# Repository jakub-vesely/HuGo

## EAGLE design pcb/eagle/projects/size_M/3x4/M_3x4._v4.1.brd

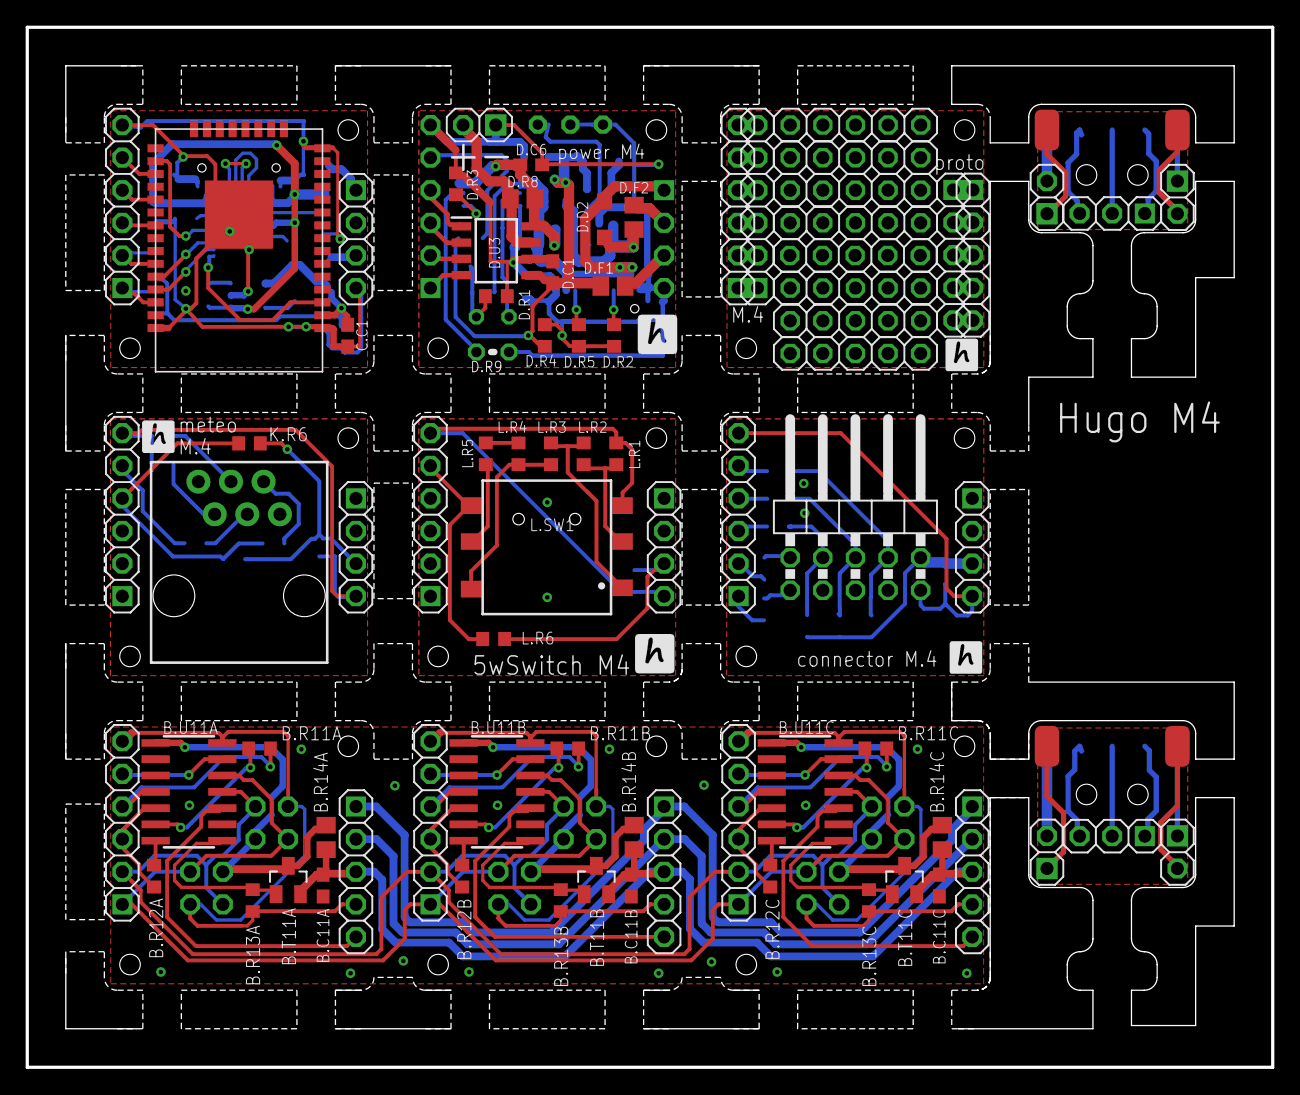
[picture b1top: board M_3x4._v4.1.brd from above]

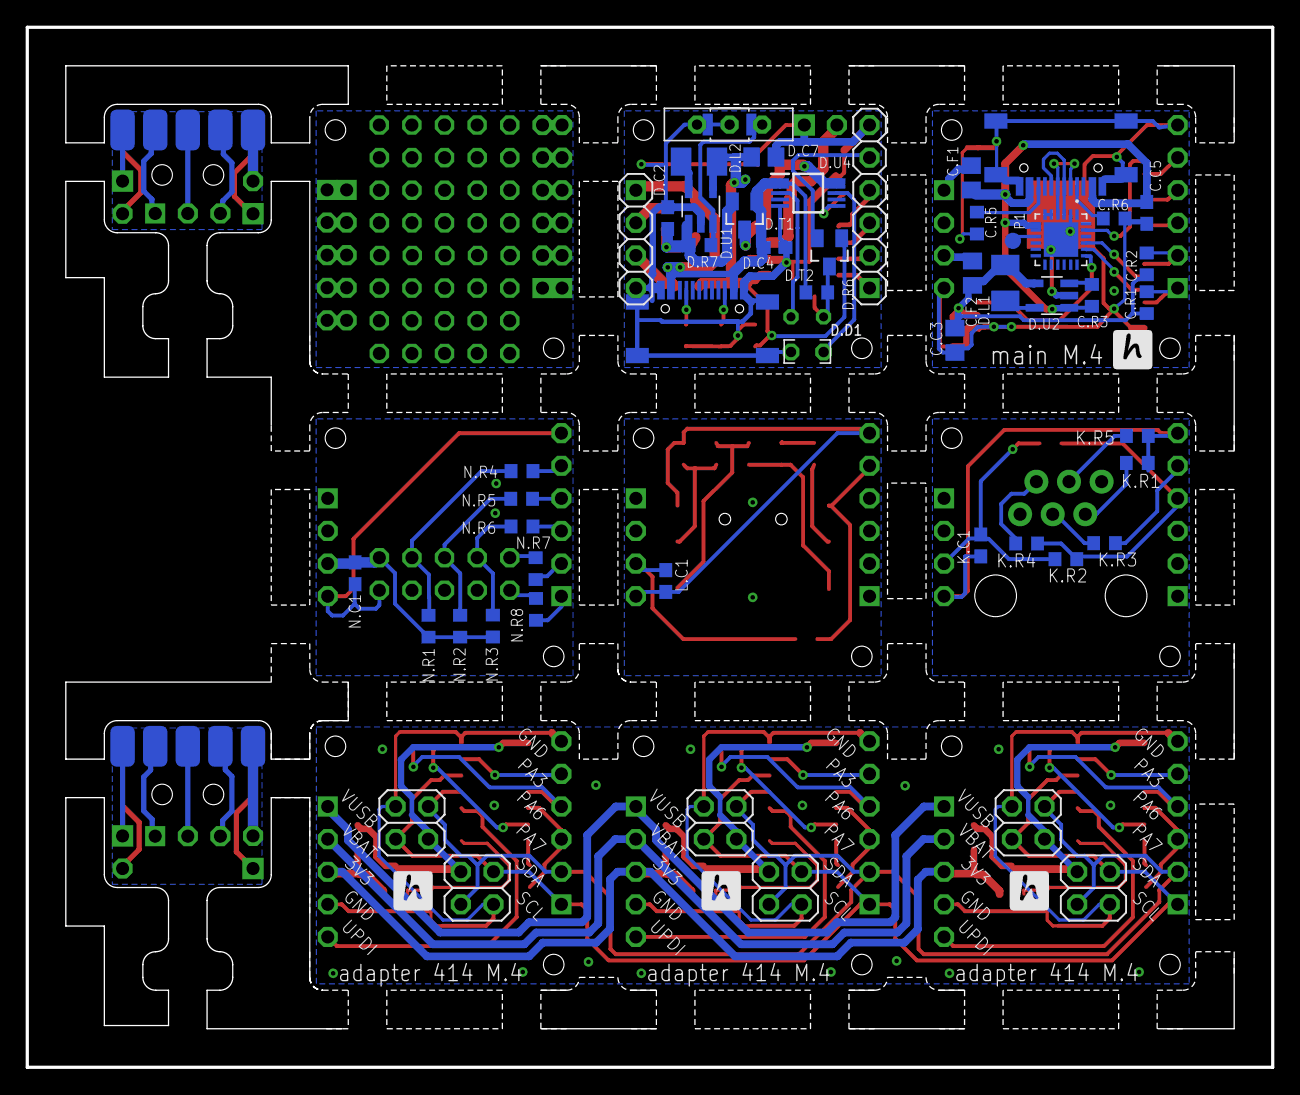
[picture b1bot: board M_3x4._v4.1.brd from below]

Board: 2 copper layers, 97.0 x 81.0 mm, 132 parts (51 on the bottom side), 125 nets.

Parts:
B.C11A, B.C11B, B.C11C: 100n; C0603
B.J1, B.J5, B.J12: 1X06
B.J2, B.J3, B.J6, B.J7, B.J13, B.J14: 2X02
B.J4, B.J8, B.J11: 1X05
B.R11A, B.R11B, B.R11C: alt RX 0R; R0603
B.R12A, B.R12B, B.R12C: alt TX 0R; R0603
B.R13A, B.R13B, B.R13C: 100k; R0603
B.R14A, B.R14B, B.R14C: alt fuse or 0R; FUSE
B.T11A, B.T11B, B.T11C: NX3008; SO23
B.U11A, B.U11B, B.U11C: AT414; SO14
C.C1: 100n; C0603
C.C3: 22u; C0805
C.C5: 1u; C0603
C.F1, C.F2: 0.5A; R0805
C.J2: 1X06
C.R1, C.R2: 2k2; R0603
C.R3: 100k; R0603
C.R5: 5K1; R0603
C.R6: 5k1; R0603
C.U1: TTGO-MICRO-32
D.C1: 100n; C0603
D.C2, D.C4, D.C6: 4u7; C0603
D.C7: 10u; C0805
D.D1: LED_1.8_FLIPPED; LED_1.8
D.D2: SHOTKY_2.8
D.F1: 0.5A; R0805
D.F2: 1.1A; R0805
D.J2: 1X06
D.J3: 1X04
D.L1, D.L2: 2u2; L3230M
D.LIPOL: 1X02
D.ON/OFF/RESET: SWITCH
D.R1: 4k7; R0603
D.R2, D.R5: 5k1; R0603
D.R3: I=1/R (4k7 for 213mA, 2k2 for455mA ); R0603
D.R4: 100k; R0603
D.R6: 3k3; R0603
D.R7: 390k; R0603
D.R8: 0.1; R0805
D.R9: TERM_10K; THERM
D.T1: FDV304; SO23
D.T2: NX3008; SO23
D.U1, D.U2: LM3671_3.3; SOT32-5
D.U3: INA219AIDR; SOIC127P600X175-8N
D.U4: MCP73833-AMI_UN; SOP50P490X110-10N
G.J1: 1X06
G.J2: 1X04
I.J1, I.J3: 1X04
J1: RJ11; RJ11-6
JP1: 1X04
JP2, JP3, JP5, JP9: 1X06
JP4, JP11: 1X05
JP6, JP12: 1X03
JP7, JP8, JP13, JP14: 1X02
JP10: 2X05/90
K.C1: 100n; C0603
K.R1, K.R3, K.R4, K.R5: 1k; R0603
K.R2, K.R6: 4k7; R0603
L.C1: 100n; C0603
L.R1, L.R2: 1k; R0603
L.R3, L.R4, L.R5, L.R6: 2k2; R0603
L.SW1: 5_WAY_SWITCH
N.C1: 100n; C0603
N.R1, N.R2, N.R3, N.R4, N.R5, N.R6, N.R7, N.R8: 4k7; R0603
P1: TPB1,27; B1,27
U1: CP2104-F03-GM; QFN50P400X400X80-25N
U$1, U$2: USB-C
U$3, U$4, U$5, U$6, U$7, U$8, U$9, U$10: PINHD-1X5_AUTO; 1X5_AUTO
U$11, U$12: 7PIN_CONNECTOR

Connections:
3V3F: D.F1.2, D.J3.3
GND: C.C1.2, C.C3.2, C.C5.1, C.J2.6, C.R5.1, C.R6.1, C.U1.GND1, C.U1.GND2, C.U1.GND3, C.U1.GND4, C.U1.GND5, C.U1.GND6, C.U1.GND7, C.U1.GND8, C.U1.GND9, C.U1.GND10, C.U1.GND11, D.U2.GND, JP1.4, U1.2, U1.25, U$1.A1B12, U$1.B1A12, U$1.SH1, U$1.SH2, U$1.SH3, U$1.SH4
GND1: D.C1.1, D.C2.1, D.C4.1, D.C6.1, D.C7.1, D.J2.6, D.J3.4, D.LIPOL.1, D.ON/OFF/RESET.P$1, D.ON/OFF/RESET.P$2, D.ON/OFF/RESET.P$4, D.R1.1, D.R2.2, D.R3.1, D.R4.2, D.R5.2, D.R9.1, D.U1.GND, D.U3.6, D.U4.5, U$2.A1B12, U$2.B1A12, U$2.SH1, U$2.SH2, U$2.SH3, U$2.SH4
GND2: JP2.6, JP3.6, JP4.4, JP11.4
GND3: G.J1.6, G.J2.4, L.C1.1, L.R1.2, L.SW1.4
GND4: I.J3.4, JP5.6, K.C1.2, K.R1.1, K.R5.1
GND5: JP7.1, U$11.7
GND6: B.C11A.2, B.C11B.2, B.C11C.2, B.J1.6, B.J2.4, B.J3.1, B.J4.4, B.J5.6, B.J6.4, B.J7.1, B.J8.4, B.J11.4, B.J12.6, B.J13.4, B.J14.1, B.R13A.2, B.R13B.2, B.R13C.2, B.U11A.14, B.U11B.14, B.U11C.14
GND7: I.J1.4, JP9.6, JP10.9, N.C1.2
GND8: JP13.1, U$12.7
IN+: D.LIPOL.2, D.R8.2, D.U3.7
IN-: D.C6.2, D.R8.1, D.T1.D, D.U3.8, D.U4.9, D.U4.10
unnamed: U1.4, U$1.A7, U$1.B7
unnamed: U1.3, U$1.A6, U$1.B6
unnamed: C.R6.2, U$1.A5
unnamed: C.R5.2, U$1.B5
unnamed: C.F2.2, JP1.3
unnamed: C.F1.2, JP1.1
unnamed: P1.TP, U1.9
unnamed: U1.5, U1.6
unnamed: D.L2.1, D.U1.VOUT
unnamed: D.L1.1, D.U2.VOUT
unnamed: C.R3.1, D.U2.SHDN
unnamed: C.J2.5, C.U1.IO4
unnamed: C.J2.4, C.U1.IO17
unnamed: C.J2.3, C.U1.IO18
unnamed: D.ON/OFF/RESET.P$3, D.ON/OFF/RESET.P$5, D.R7.2, D.U1.SHDN
unnamed: D.R5.1, U$2.B5
unnamed: D.R2.1, U$2.A5
unnamed: D.R3.2, D.U4.6
unnamed: D.R9.2, D.U4.8
unnamed: D.J2.5, D.T2.S
unnamed: JP2.5, JP3.5
unnamed: JP2.4, JP3.4
unnamed: JP2.3, JP3.3
unnamed: JP2.2, JP3.2
unnamed: JP2.1, JP3.1
unnamed: JP4.5, JP11.5
unnamed: JP4.2, JP11.2
unnamed: JP4.1, JP11.1
unnamed: JP4.3, JP11.3
unnamed: L.R1.1, L.R2.2, L.SW1.5
unnamed: L.R2.1, L.R3.2, L.SW1.6
unnamed: L.R3.1, L.R4.2, L.SW1.3
unnamed: L.R5.2, L.SW1.2
unnamed: G.J1.5, L.R6.1, L.SW1.1
unnamed: L.R4.1, L.R5.1
unnamed: JP5.5, K.R3.1
unnamed: JP5.4, K.R2.2, K.R4.1, K.R6.2
unnamed: J1.5, K.R4.2
unnamed: J1.4, K.R3.2
unnamed: J1.3, K.R5.2
unnamed: J1.2, K.R1.2
unnamed: B.R12A.2, B.U11A.7
unnamed: B.R11A.2, B.U11A.6
unnamed: B.R13A.1, B.T11A.G, B.U11A.8
unnamed: B.R12C.2, B.U11C.7
unnamed: B.C11A.1, B.C11B.1, B.C11C.1, B.J4.3, B.J8.3, B.J11.3, B.R14A.1, B.R14B.1, B.R14C.1, B.T11A.S, B.T11B.S, B.T11C.S
unnamed: B.R12B.2, B.U11B.7
unnamed: B.R11B.2, B.U11B.6
unnamed: B.R13B.1, B.T11B.G, B.U11B.8
unnamed: B.R11C.2, B.U11C.6
unnamed: B.R13C.1, B.T11C.G, B.U11C.8
unnamed: JP8.1, U$11.2
unnamed: JP8.2, U$11.1
unnamed: JP6.2, U$11.4
unnamed: JP6.3, U$11.5
unnamed: JP6.1, U$11.3
unnamed: JP10.8, N.R1.2, N.R4.2
unnamed: JP10.6, N.R2.2, N.R5.2
unnamed: JP10.2, N.R7.2
unnamed: JP9.5, N.R4.1
unnamed: JP9.4, N.R5.1
unnamed: JP9.3, N.R6.1
unnamed: JP9.2, N.R7.1
unnamed: JP9.1, N.R8.1
unnamed: JP10.1, N.R8.2
unnamed: JP10.4, N.R3.2, N.R6.2
unnamed: JP14.1, U$12.2
unnamed: JP14.2, U$12.1
unnamed: JP12.2, U$12.4
unnamed: JP12.3, U$12.5
unnamed: JP12.1, U$12.3
PA1: B.J12.5, B.U11A.13
PA2: B.J12.4, B.R11A.1, B.U11A.4
PA3: D.D1.1, D.R1.2, D.R6.1, D.T2.D
PA4: B.J12.3, B.R12A.1, B.U11A.5
PA5: B.J1.5, B.U11B.13
PA6: D.J2.4, D.U3.1
PA7: D.J2.3, D.U3.2
PA8: B.J1.4, B.R11B.1, B.U11B.4
PA9: B.J1.3, B.R12B.1, B.U11B.5
PA10: B.J5.5, B.U11C.13
PA11: B.J5.4, B.R11C.1, B.U11C.4
PA12: B.J5.3, B.R12C.1, B.U11C.5
PROG: C.U1.IO0, U1.23
RESET: C.U1.EN, U1.19
RX: C.U1.TXD0, U1.20
SCL: C.J2.1, C.R1.1, C.U1.IO22
SCL1: D.J2.1, D.U3.4
SCL2: B.J1.1, B.J2.2, B.J3.3, B.J5.1, B.J6.2, B.J7.3, B.J12.1, B.J13.2, B.J14.3, B.U11A.12, B.U11B.12, B.U11C.12
SDA: C.J2.2, C.R2.1, C.U1.IO21
SDA1: D.J2.2, D.U3.3
SDA2: B.J1.2, B.J2.3, B.J3.2, B.J5.2, B.J6.3, B.J7.2, B.J12.2, B.J13.3, B.J14.2, B.U11A.11, B.U11B.11, B.U11C.11
STAT1: D.D1.2, D.U4.3
TX: C.U1.RXD0, U1.21
UPDI: B.J11.5, B.U11A.10
UPDI1: B.J4.5, B.U11B.10
UPDI2: B.J8.5, B.U11C.10
VBAT: B.J4.2, B.J8.2, B.J11.2
VBATF: D.F2.2, D.J3.2
VCC: C.C1.1, C.C3.1, C.F2.1, C.R1.2, C.R2.2, C.U1.3V3, D.L1.2, D.U2.BP
VCC1: D.C1.2, D.C7.2, D.F1.1, D.L2.2, D.R4.1, D.T2.G, D.U1.BP, D.U3.5
VCC2: G.J2.3, L.C1.2, L.R6.2
VCC3: I.J3.3, K.C1.1, K.R2.1, K.R6.1
VCC4: B.J13.1, B.J14.4, B.R14A.2, B.T11A.D, B.U11A.1
VCC5: B.J2.1, B.J3.4, B.R14B.2, B.T11B.D, B.U11B.1
VCC6: B.J6.1, B.J7.4, B.R14C.2, B.T11C.D, B.U11C.1
VCC7: JP7.2, U$11.6
VCC8: I.J1.3, JP10.10, N.C1.1, N.R1.1, N.R2.1, N.R3.1
VCC9: JP13.2, U$12.6
VMOT: D.C2.2, D.D2.K, D.F2.1, D.R7.1, D.T1.S, D.U1.VIN
VUSB: C.C5.2, C.F1.1, C.R3.2, D.U2.VIN, U1.7, U1.8, U$1.A4B9, U$1.B4A9
VUSB1: D.C4.2, D.D2.A, D.J3.1, D.R6.2, D.T1.G, D.U4.1, D.U4.2, U$2.A4B9, U$2.B4A9
VUSB2: B.J4.1, B.J8.1, B.J11.1

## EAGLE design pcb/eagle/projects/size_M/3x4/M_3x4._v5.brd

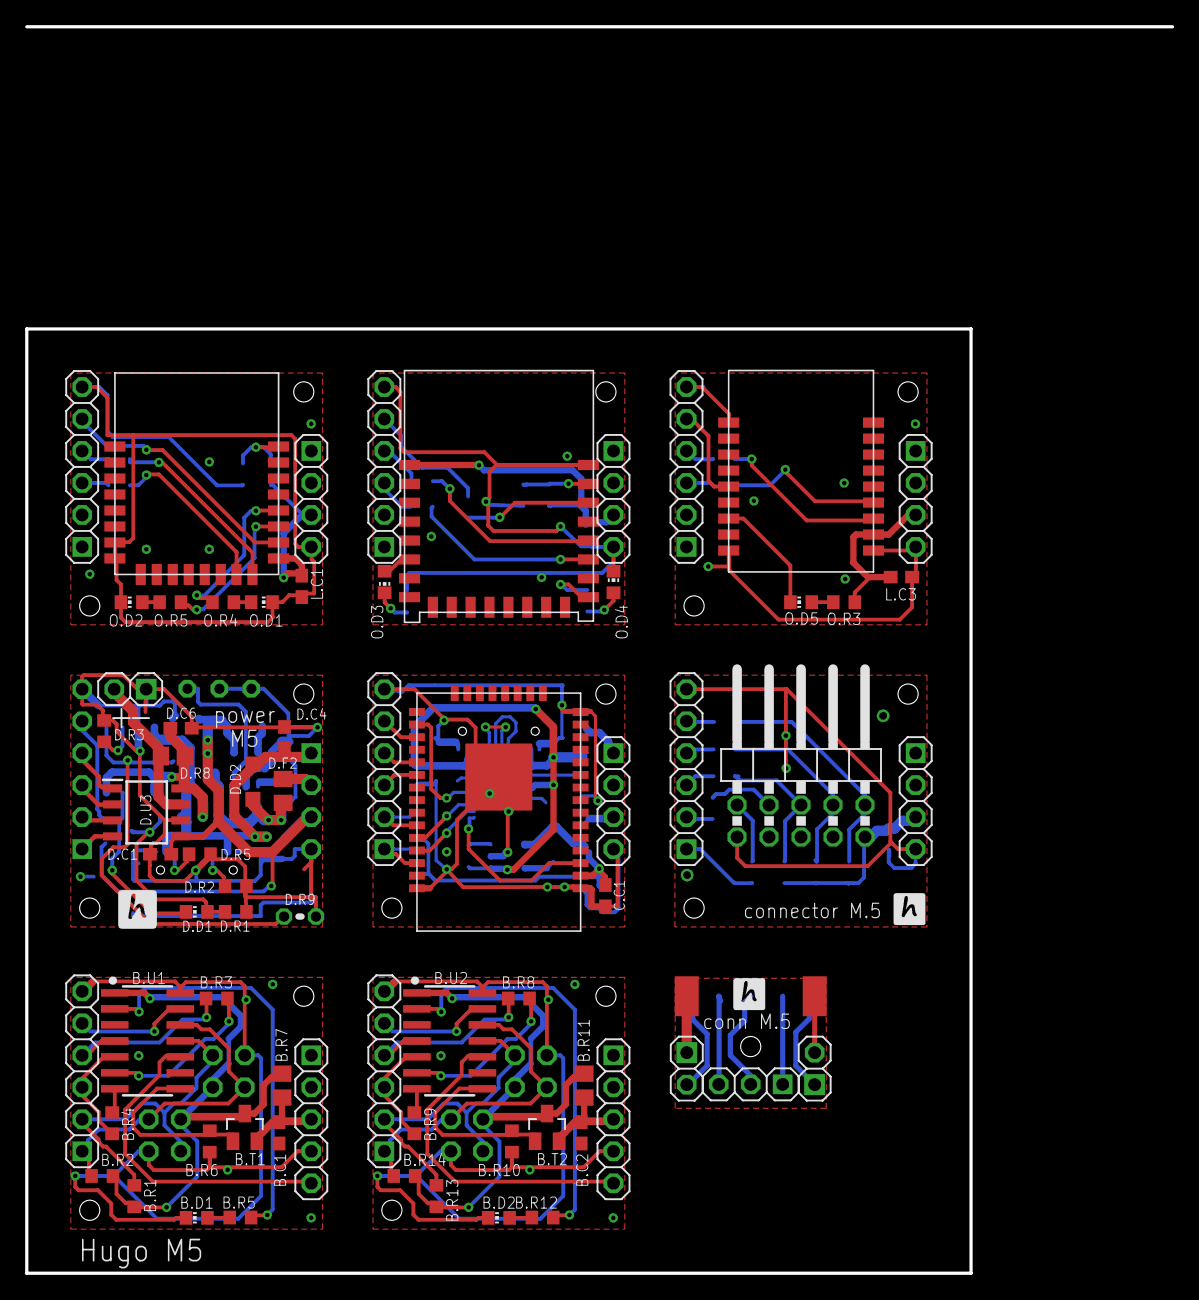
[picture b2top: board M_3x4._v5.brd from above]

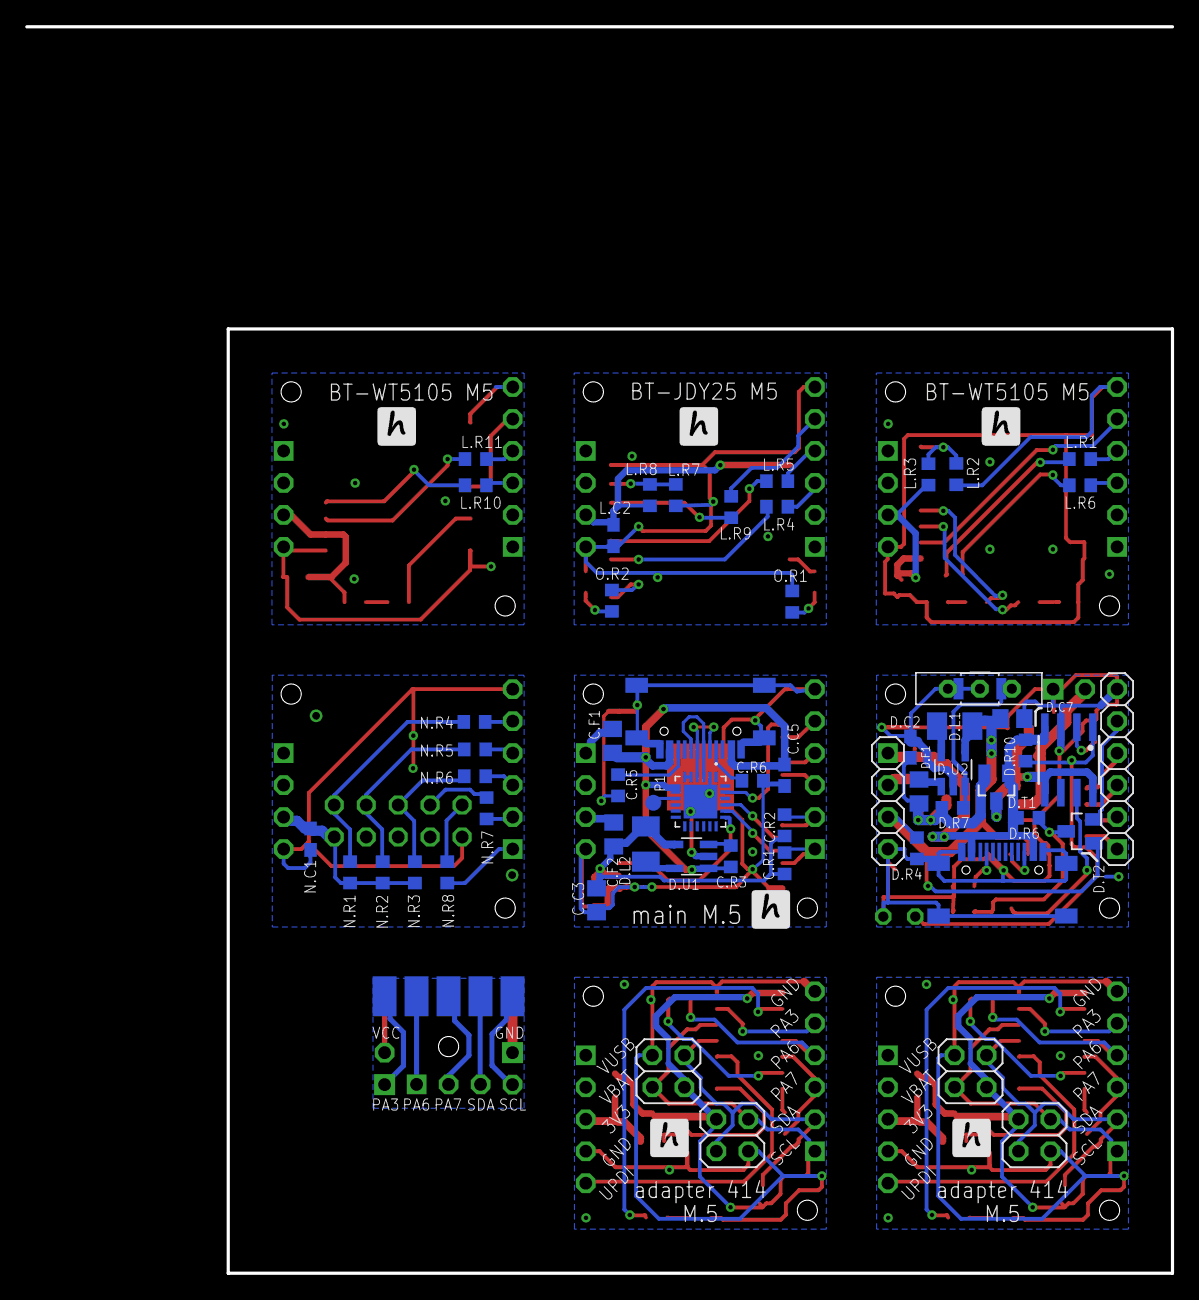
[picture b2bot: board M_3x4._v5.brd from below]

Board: 2 copper layers, 75.0 x 75.0 mm, 127 parts (57 on the bottom side), 124 nets.

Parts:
B.C1, B.C2: 100n; C0603
B.D1, B.D2: CHIP-LED0603
B.J1, B.J8: 1X05
B.J2, B.J5: 1X06
B.J3, B.J4, B.J6, B.J7: 2X02
B.R1, B.R2, B.R13, B.R14: 2k2; R0603
B.R3, B.R8: alt RX 0R; R0603
B.R4, B.R9: alt TX 0R; R0603
B.R5, B.R12: 3k3; R0603
B.R6, B.R10: 100k; R0603
B.R7, B.R11: alt fuse or 0R; FUSE
B.T1, B.T2: NX3008; SO23
B.U1, B.U2: AT414; SO14
C.C1: 100n; C0603
C.C3: 22u; C0805
C.C5: 4u7; C0603
C.F1, C.F2: 0.5A; R0805
C.J2: 1X06
C.R1, C.R2: 2k2; R0603
C.R3: 100k; R0603
C.R5: 5K1; R0603
C.R6: 5k1; R0603
C.U1: TTGO-MICRO-32
D.C1: 100n; C0603
D.C2, D.C4, D.C6: 4u7; C0603
D.C7: 10u; C0805
D.D1: CHIP-LED0603
D.D2: SHOTKY_2.8
D.F1: 0.5A; R0805
D.F2: 1.1A; R0805
D.J2: 1X06
D.J3: 1X04
D.L1, D.L2: 4u7; L3230M
D.LIPOL: 1X02
D.ON/OFF/RESET: SWITCH
D.R1: 4k7; R0603
D.R2, D.R5: 5k1; R0603
D.R3: I=1800/R (10k for 0.2A, 3k3 for 0.55A, 3k9 for 0.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; R0603
D.R4: 100k; R0603
D.R6: 3k3; R0603
D.R7: 390k; R0603
D.R8: 0.1; R0805
D.R9: TERM_10K; THERM
D.R10: 10k?; R0603
D.T1: FDV304; SO23
D.T2: NX3008; SO23
D.U1, D.U2: MCP1603T-330I; SOT32-5
D.U3: INA219AIDR; SOIC127P600X175-8N
G.J1, G.J3, G.J5: 1X06
G.J2, G.J4, G.J6: 1X04
I.J3: 1X04
JP1: 1X03
JP2: 1X06
JP3: 1X04
JP4: 2X05/90
JP5, JP6: 1X02
L.C1, L.C2, L.C3: 100n; C0603
L.R1, L.R2, L.R3, L.R4, L.R5, L.R6, L.R7, L.R8, L.R9, L.R10, L.R11: 2k2; R0603
N.C1: 100n; C0603
N.R1, N.R2, N.R3, N.R4, N.R5, N.R6, N.R7, N.R8: 4k7; R0603
O.D1, O.D2, O.D3, O.D4, O.D5: CHIP-LED0603
O.R1, O.R2, O.R3, O.R4, O.R5: 2k2; R0603
P1: TPB1,27; B1,27
U1: CP2104-F03-GM; QFN50P400X400X80-25N
U$1: 7PIN_CONNECTOR
U$2, U$4: USB-C
U$3: CN3083; SOP8
U$5: WT5105-M1
U$6: JDY-25
U$7: E104-BT5011A

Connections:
GND: I.J3.4, JP2.6, JP4.1, N.C1.2
GND1: JP5.1, U$1.7
GND2: D.C1.1, D.C2.1, D.C4.1, D.C6.1, D.C7.1, D.J2.6, D.J3.4, D.LIPOL.1, D.ON/OFF/RESET.P$1, D.ON/OFF/RESET.P$2, D.ON/OFF/RESET.P$4, D.R1.1, D.R2.2, D.R3.1, D.R4.2, D.R5.2, D.R9.1, D.U2.GND, D.U3.6, U$2.A1B12, U$2.B1A12, U$2.SH1, U$2.SH2, U$2.SH3, U$2.SH4, U$3.3
GND3: B.C1.2, B.D1.C1, B.J1.4, B.J2.6, B.J3.4, B.J4.1, B.R6.2, B.U1.14
GND4: B.C2.2, B.D2.C1, B.J5.6, B.J6.4, B.J7.1, B.J8.4, B.R10.2, B.U2.14
GND6: C.C1.2, C.C3.2, C.C5.1, C.J2.6, C.R5.1, C.R6.1, C.U1.GND1, C.U1.GND2, C.U1.GND3, C.U1.GND4, C.U1.GND5, C.U1.GND6, C.U1.GND7, C.U1.GND8, C.U1.GND9, C.U1.GND10, C.U1.GND11, D.U1.GND, JP3.4, U1.2, U1.25, U$4.A1B12, U$4.B1A12, U$4.SH1, U$4.SH2, U$4.SH3, U$4.SH4
GND7: G.J1.6, G.J2.4, L.C1.1, L.R2.1, O.D1.C1, O.D2.C1, U$5.GND1, U$5.GND2
GND8: G.J3.6, G.J4.4, L.C2.1, L.R7.1, O.D4.C1, O.R1.1, U$6.GND
GND9: G.J5.6, G.J6.4, L.C3.1, U$7.GND1, U$7.GND2, U$7.GND3
IN+: D.LIPOL.2, D.R8.2, D.U3.7
IN-: D.C6.2, D.R8.1, D.T1.D, D.U3.8, U$3.5, U$3.8
unnamed: D.L1.1, D.U2.VOUT
unnamed: JP4.10, N.R1.2, N.R4.2
unnamed: JP4.8, N.R2.2, N.R5.2
unnamed: JP2.5, N.R4.1
unnamed: JP2.4, N.R5.1
unnamed: JP2.3, N.R6.1
unnamed: JP2.2, N.R7.1
unnamed: JP2.1, N.R8.1
unnamed: JP4.6, N.R3.2, N.R6.2
unnamed: JP4.4, N.R7.2
unnamed: JP4.2, N.R8.2
unnamed: D.ON/OFF/RESET.P$3, D.ON/OFF/RESET.P$5, D.R7.2, D.U2.SHDN
unnamed: D.R5.1, U$2.B5
unnamed: D.R2.1, U$2.A5
unnamed: D.R3.2, U$3.2
unnamed: D.J2.5, D.T2.S
unnamed: D.D1.C1, U$3.7
unnamed: D.R9.2, D.R10.1, U$3.1
unnamed: D.F1.2, D.U2.VIN
unnamed: B.R4.2, B.U1.7
unnamed: B.R3.2, B.U1.6
unnamed: B.R6.1, B.T1.G, B.U1.8
unnamed: B.C1.1, B.J1.3, B.R7.1, B.T1.S
unnamed: B.R5.2, B.U1.2
unnamed: B.R9.2, B.U2.7
unnamed: B.R8.2, B.U2.6
unnamed: B.R10.1, B.T2.G, B.U2.8
unnamed: B.C2.1, B.J8.3, B.R11.1, B.T2.S
unnamed: B.R12.2, B.U2.2
unnamed: U1.4, U$4.A7, U$4.B7
unnamed: U1.3, U$4.A6, U$4.B6
unnamed: C.R6.2, U$4.A5
unnamed: C.R5.2, U$4.B5
unnamed: C.F2.2, JP3.3
unnamed: C.F1.2, JP3.1
unnamed: P1.TP, U1.9
unnamed: U1.5, U1.6
unnamed: D.L2.1, D.U1.VOUT
unnamed: C.R3.1, D.U1.SHDN
unnamed: C.J2.5, C.U1.IO4
unnamed: C.J2.4, C.U1.IO17
unnamed: C.J2.3, C.U1.IO5
unnamed: L.R6.1, U$5.P09
unnamed: G.J1.4, L.R1.2
unnamed: L.R1.1, U$5.P10
unnamed: G.J1.5, U$5.P14
unnamed: L.R2.2, L.R3.2, U$5.RST
unnamed: O.R4.2, U$5.P20
unnamed: O.R5.2, U$5.P15
unnamed: O.D1.A1, O.R4.1
unnamed: O.D2.A1, O.R5.1
unnamed: L.R7.2, L.R8.2, U$6.RST
unnamed: L.R5.1, U$6.RXD
unnamed: L.R4.1, U$6.TXD
unnamed: G.J3.5, L.R9.2
unnamed: L.R9.1, U$6.PWRC
unnamed: O.D4.A1, O.R2.1
unnamed: O.R2.2, U$6.ALED
unnamed: O.D3.A1, U$6.STAT
unnamed: O.D3.C1, O.R1.2
unnamed: G.J5.4, L.R11.2
unnamed: O.D5.A1, O.R3.1
unnamed: L.R10.1, U$7.TXD
unnamed: L.R11.1, U$7.RXD
unnamed: G.J5.5, U$7.WKP
unnamed: O.D5.C1, U$7.LINK
PA1: D.J2.4, D.U3.1
PA2: D.J2.3, D.U3.2
PA3: JP6.1, U$1.2
PA4: D.D1.A1, D.R1.2, D.R6.1, D.T2.D
PA5: B.J2.5, B.U1.13
PA6: JP1.1, U$1.3
PA7: JP1.2, U$1.4
PA8: B.J2.4, B.R3.1, B.U1.4
PA9: B.J2.3, B.R4.1, B.U1.5
PA10: B.D1.A1, B.R5.1
PA11: B.J5.5, B.U2.13
PA12: B.J5.4, B.R8.1, B.U2.4
PA13: B.J5.3, B.R9.1, B.U2.5
PA14: B.D2.A1, B.R12.1
PROG: C.U1.IO0, U1.23
RESET: C.U1.EN, U1.19
RX: C.U1.TXD0, U1.20
RX1: G.J3.3, L.R4.2
SCL: D.J2.1, D.U3.4
SCL1: JP5.2, U$1.6
SCL2: B.J2.1, B.J3.2, B.J4.3, B.R2.1, B.U1.12
SCL3: B.J5.1, B.J6.2, B.J7.3, B.R14.1, B.U2.12
SCL5: C.J2.1, C.R1.1, C.U1.IO22
SDA: D.J2.2, D.U3.3
SDA1: JP1.3, U$1.5
SDA2: B.J2.2, B.J3.3, B.J4.2, B.R1.1, B.U1.11
SDA3: B.J5.2, B.J6.3, B.J7.2, B.R13.1, B.U2.11
SDA5: C.J2.2, C.R2.1, C.U1.IO21
TX: C.U1.RXD0, U1.21
TX1: G.J3.4, L.R5.2
UPDI: B.J1.5, B.U1.10
UPDI1: B.J8.5, B.U2.10
VBATF: D.F2.2, D.J3.2
VCC: I.J3.3, JP4.9, N.C1.1, N.R1.1, N.R2.1, N.R3.1
VCC1: JP6.2, U$1.1
VCC2: D.C1.2, D.C7.2, D.J3.3, D.L1.2, D.R4.1, D.T2.G, D.U2.BP, D.U3.5
VCC3: B.J3.1, B.J4.4, B.R1.2, B.R2.2, B.R7.2, B.T1.D, B.U1.1
VCC4: B.J6.1, B.J7.4, B.R11.2, B.R13.2, B.R14.2, B.T2.D, B.U2.1
VCC6: C.C1.1, C.C3.1, C.F2.1, C.R1.2, C.R2.2, C.U1.3V3, D.L2.2, D.U1.BP
VCC7: G.J2.3, L.C1.2, L.R3.1, U$5.VCC
VCC8: G.J1.3, L.R6.2
VCC9: G.J4.3, L.C2.2, L.R8.1, U$6.VCC
VCC10: G.J6.3, L.C3.2, O.R3.2, U$7.VCC
VCC11: G.J5.3, L.R10.2
VMOT: D.C2.2, D.D2.K, D.F1.1, D.F2.1, D.R7.1, D.T1.S
VUSB: D.C4.2, D.D2.A, D.J3.1, D.R6.2, D.R10.2, D.T1.G, U$2.A4B9, U$2.B4A9, U$3.4
VUSB4: C.C5.2, C.F1.1, C.R3.2, D.U1.VIN, U1.7, U1.8, U$4.A4B9, U$4.B4A9

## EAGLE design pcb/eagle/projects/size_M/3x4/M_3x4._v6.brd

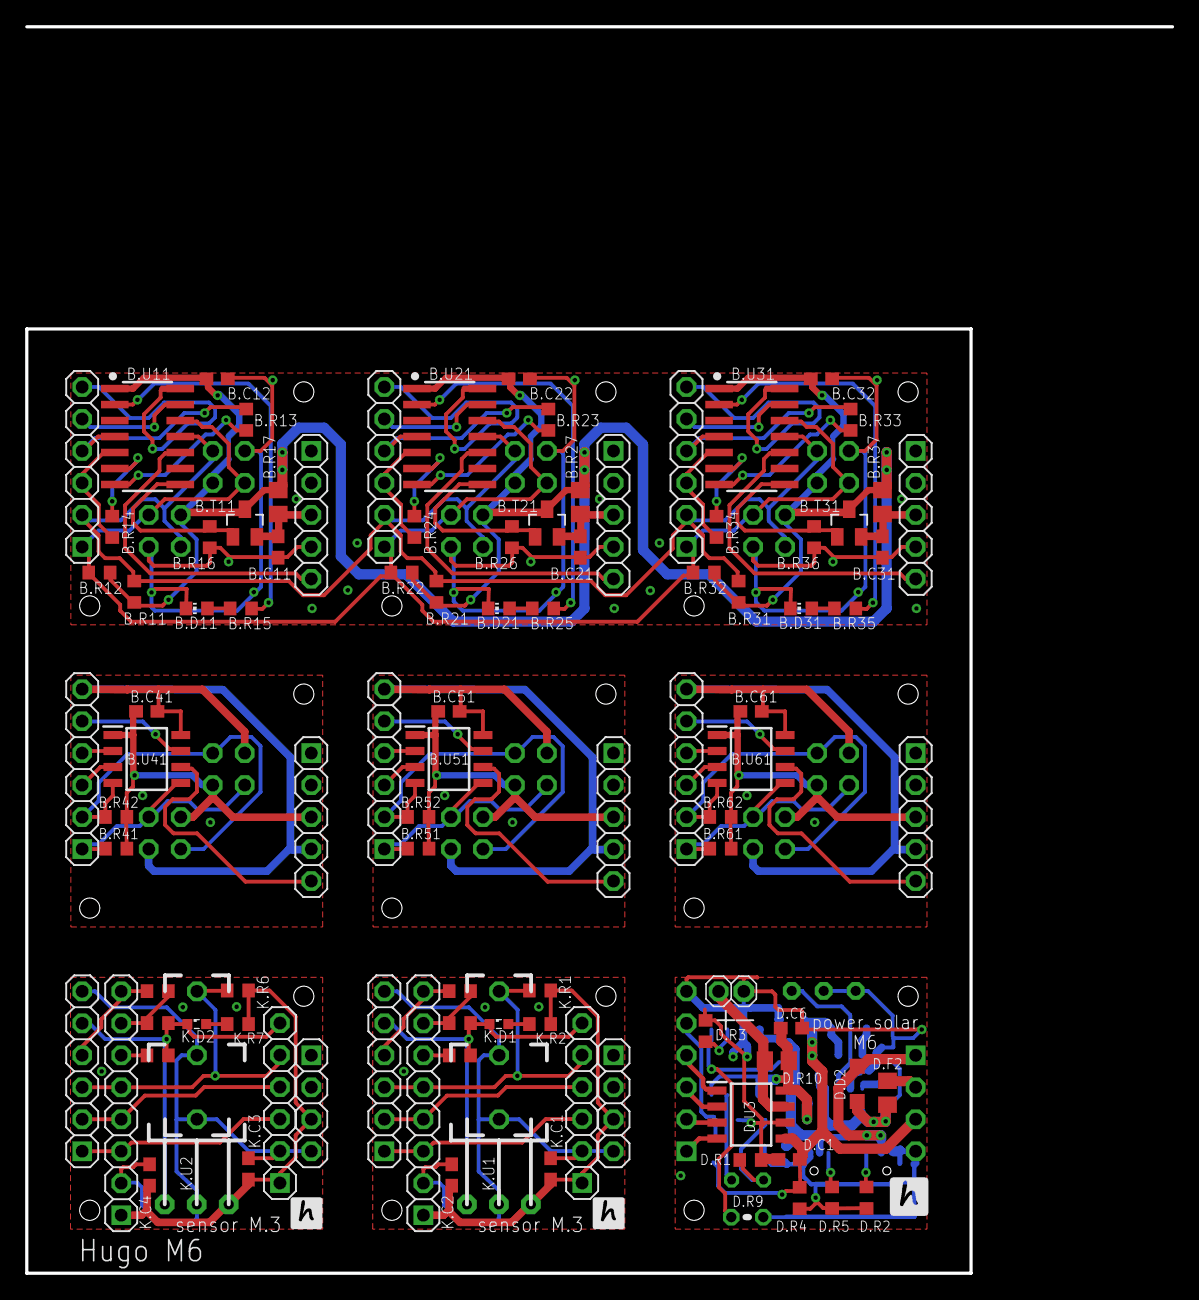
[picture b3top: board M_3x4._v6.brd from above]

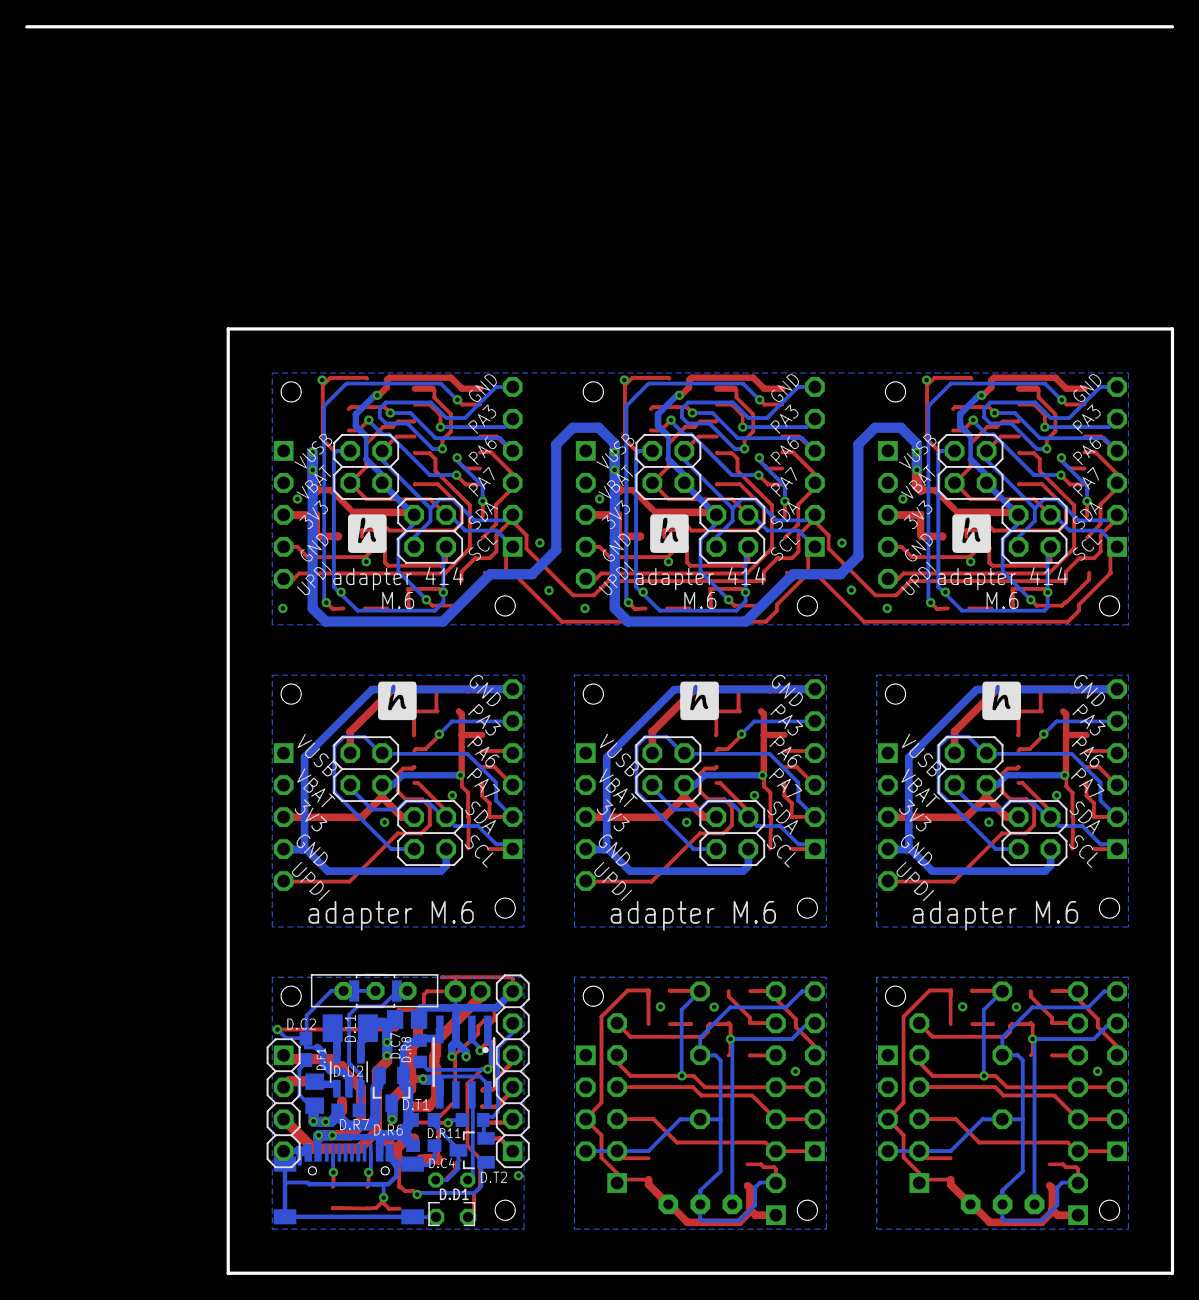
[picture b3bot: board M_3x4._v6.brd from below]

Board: 2 copper layers, 75.0 x 75.0 mm, 131 parts (30 on the bottom side), 99 nets.

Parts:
B.C11, B.C12, B.C21, B.C22, B.C31, B.C32, B.C41, B.C51, B.C61: 100n; C0603
B.D11, B.D21, B.D31: CHIP-LED0603
B.J1, B.J8, B.J12, B.J15, B.J18, B.J21: 1X05
B.J2, B.J5, B.J9, B.J13, B.J16, B.J19: 1X06
B.J3, B.J4, B.J6, B.J7, B.J10, B.J11, B.J14, B.J17, B.J20: 2X02
B.R11, B.R12, B.R21, B.R22, B.R31, B.R32: 2k2; R0603
B.R13, B.R23, B.R33: alt RX 0R; R0603
B.R14, B.R24, B.R34: alt TX 0R; R0603
B.R15, B.R25, B.R35: 1k; R0603
B.R16, B.R26, B.R36: 100k; R0603
B.R17, B.R27, B.R37: alt fuse or 0R; FUSE
B.R41, B.R42, B.R51, B.R52, B.R61, B.R62: alt 2k2 for master; R0603
B.T11, B.T21, B.T31: NX3008; SO23
B.U11, B.U21, B.U31: AT414; SO14
B.U41, B.U51, B.U61: AT412; SOIC127P600X175-8N
D.C1: 100n; C0603
D.C2, D.C4, D.C6: 4u7; C0603
D.C7: 10u; C0805
D.D1: LED_1.8
D.D2: SHOTKY_2.8
D.F1: 0.5A; R0805
D.F2: 1.1A; R0805
D.J2: 1X06
D.J3: 1X04
D.L1: 2u2; L3230M
D.LIPOL: 1X02-2
D.ON/OFF/RESET: SWITCH
D.R1: 4k7; R0603
D.R2, D.R5: 5k1; R0603
D.R3: I=1800/R (10k for 0.2A, 3k3 for 0.55A, 3k9 for 0.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; R0603
D.R4, D.R11: 100k; R0603
D.R6: 3k3; R0603
D.R7: 390k; R0603
D.R8: 10k?; R0603
D.R9: TERM_10K; THERM
D.R10: 0.1; R0805
D.T1: FDV304; SO23
D.T2: NX3008; SO23
D.U2: LM3671_3.3; SOT32-5
D.U3: INA219AIDR; SOIC127P600X175-8N
I.J1, I.J3: 1X04
JB1, JB2, JB3: 2X02
JP1, JP2, JP4, JP6: 1X06
JP3, JP5: 1X08
K.C1, K.C2, K.C3, K.C4: C0603
K.D1, K.D2: SML0603
K.R1, K.R6: 100K; R0603
K.R2, K.R7: 180R; R0603
K.R3, K.R4, K.R5, K.R8, K.R9, K.R10: 0R; R0603
K.U1, K.U2: VS1838B; IR_RECEIVER
U$1, U$2: BUTTON-SWITCH
U$3: USB-C
U$4: CN3083; SOP8

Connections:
3V1: B.C51.1, B.J17.4, B.J18.3, B.R51.2, B.R52.2, B.U51.1, JB1.1
3V2: B.C61.1, B.J20.4, B.J21.3, B.R61.2, B.R62.2, B.U61.1, JB2.1
3V3: B.C41.1, B.J14.4, B.J15.3, B.R41.2, B.R42.2, B.U41.1, JB3.1
GND: B.C11.2, B.C12.2, B.C21.2, B.C22.2, B.C31.2, B.C32.2, B.D11.C1, B.D21.C1, B.D31.C1, B.J1.4, B.J2.6, B.J3.4, B.J4.1, B.J5.6, B.J6.4, B.J7.1, B.J8.4, B.J9.6, B.J10.4, B.J11.1, B.J12.4, B.R16.2, B.R26.2, B.R36.2, B.U11.14, B.U21.14, B.U31.14
GND1: I.J3.4, JP1.2, JP2.6, JP3.2, K.C1.2, K.C2.2, K.U1.GND, U$2.P$1, U$2.P$2
GND2: B.C41.2, B.J13.6, B.J14.1, B.J15.4, B.U41.8, JB3.4
GND3: B.C51.2, B.J16.6, B.J17.1, B.J18.4, B.U51.8, JB1.4
GND4: I.J1.4, JP4.6, JP5.2, JP6.2, K.C3.2, K.C4.2, K.U2.GND, U$1.P$1, U$1.P$2
GND5: D.C1.1, D.C2.1, D.C4.1, D.C6.1, D.C7.1, D.J2.6, D.J3.4, D.LIPOL.1, D.ON/OFF/RESET.P$1, D.ON/OFF/RESET.P$2, D.ON/OFF/RESET.P$4, D.R1.1, D.R2.2, D.R3.1, D.R4.2, D.R5.2, D.R9.1, D.R11.2, D.U2.GND, D.U3.6, U$3.A1B12, U$3.B1A12, U$3.SH1, U$3.SH2, U$3.SH3, U$3.SH4, U$4.3
GND6: B.C61.2, B.J19.6, B.J20.1, B.J21.4, B.U61.8, JB2.4
IN+: D.LIPOL.2, D.R10.2, D.U3.7
IN-: D.C6.2, D.R10.1, D.T1.D, D.U3.8, U$4.5, U$4.8
unnamed: B.R14.2, B.U11.6
unnamed: B.R13.2, B.U11.7
unnamed: B.R16.1, B.T11.G, B.U11.8
unnamed: B.C11.1, B.J1.3, B.R17.1, B.T11.S
unnamed: B.R15.2, B.U11.2
unnamed: B.R26.1, B.T21.G, B.U21.8
unnamed: B.C21.1, B.J8.3, B.R27.1, B.T21.S
unnamed: B.R25.2, B.U21.2
unnamed: B.R24.2, B.U21.6
unnamed: B.R23.2, B.U21.7
unnamed: B.R36.1, B.T31.G, B.U31.8
unnamed: B.C31.1, B.J12.3, B.R37.1, B.T31.S
unnamed: B.R35.2, B.U31.2
unnamed: B.R34.2, B.U31.6
unnamed: B.R33.2, B.U31.7
unnamed: JP1.4, JP2.2, JP3.4
unnamed: JP1.3, JP2.1, JP3.3
unnamed: K.D1.A, K.R2.2
unnamed: JP1.6, JP2.5, K.D1.C, K.R3.1, K.R4.1, K.U1.OUT
unnamed: JP1.5, JP2.3, JP3.5, K.R1.2, U$2.P$3
unnamed: JP2.4, JP3.8, K.R5.1
unnamed: JP3.6, K.R4.2
unnamed: JP3.7, K.R3.2, K.R5.2
unnamed: JP4.2, JP5.4, JP6.4
unnamed: JP4.1, JP5.3, JP6.3
unnamed: K.D2.A, K.R7.2
unnamed: JP4.5, JP6.6, K.D2.C, K.R8.1, K.R9.1, K.U2.OUT
unnamed: JP4.3, JP5.5, JP6.5, K.R6.2, U$1.P$3
unnamed: JP4.4, JP5.8, K.R10.1
unnamed: JP5.6, K.R9.2
unnamed: JP5.7, K.R8.2, K.R10.2
unnamed: D.L1.1, D.U2.VOUT
unnamed: D.ON/OFF/RESET.P$3, D.ON/OFF/RESET.P$5, D.R7.2, D.U2.SHDN
unnamed: D.R5.1, U$3.B5
unnamed: D.R2.1, U$3.A5
unnamed: D.R3.2, U$4.2
unnamed: D.J2.5, D.R11.1, D.T2.S
unnamed: D.D1.1, U$4.7
unnamed: D.R8.1, D.R9.2, U$4.1
unnamed: D.F1.2, D.U2.VIN
PA1: B.D11.A1, B.R15.1
PA2: B.J5.5, B.U21.13
PA3: B.J2.5, B.U11.13
PA4: B.J5.4, B.R23.1, B.U21.4
PA5: B.J5.3, B.R24.1, B.U21.5
PA6: B.J2.4, B.R13.1, B.U11.4
PA7: B.J2.3, B.R14.1, B.U11.5
PA8: B.D21.A1, B.R25.1
PA9: B.J9.5, B.U31.13
PA10: B.J9.4, B.R33.1, B.U31.4
PA11: B.J9.3, B.R34.1, B.U31.5
PA12: B.D31.A1, B.R35.1
PA13: B.J13.5, B.U41.7
PA14: B.J13.4, B.U41.2
PA15: B.J13.3, B.U41.3
PA16: B.J16.5, B.U51.7
PA17: B.J16.4, B.U51.2
PA18: B.J16.3, B.U51.3
PA19: D.J2.4, D.U3.1
PA20: D.J2.3, D.U3.2
PA21: D.D1.2, D.R1.2, D.R6.1, D.T2.D
PA22: B.J19.5, B.U61.7
PA23: B.J19.4, B.U61.2
PA24: B.J19.3, B.U61.3
SCL: B.J2.1, B.J3.2, B.J4.3, B.J5.1, B.J6.2, B.J7.3, B.J9.1, B.J10.2, B.J11.3, B.R12.1, B.R22.1, B.R32.1, B.U11.12, B.U21.12, B.U31.12
SCL1: B.J13.1, B.J14.3, B.R41.1, B.U41.5, JB3.2
SCL2: B.J16.1, B.J17.3, B.R51.1, B.U51.5, JB1.2
SCL3: D.J2.1, D.U3.4
SCL4: B.J19.1, B.J20.3, B.R61.1, B.U61.5, JB2.2
SDA: B.J2.2, B.J3.3, B.J4.2, B.J5.2, B.J6.3, B.J7.2, B.J9.2, B.J10.3, B.J11.2, B.R11.1, B.R21.1, B.R31.1, B.U11.11, B.U21.11, B.U31.11
SDA1: B.J13.2, B.J14.2, B.R42.1, B.U41.4, JB3.3
SDA2: B.J16.2, B.J17.2, B.R52.1, B.U51.4, JB1.3
SDA3: D.J2.2, D.U3.3
SDA4: B.J19.2, B.J20.2, B.R62.1, B.U61.4, JB2.3
UPDI: B.J1.5, B.U11.10
UPDI1: B.J8.5, B.U21.10
UPDI2: B.J12.5, B.U31.10
UPDI3: B.J15.5, B.U41.6
UPDI4: B.J18.5, B.U51.6
UPDI5: B.J21.5, B.U61.6
VBATF: D.F2.2, D.J3.2
VCC: B.C12.1, B.C22.1, B.C32.1, B.J3.1, B.J4.4, B.J6.1, B.J7.4, B.J10.1, B.J11.4, B.R11.2, B.R12.2, B.R17.2, B.R21.2, B.R22.2, B.R27.2, B.R31.2, B.R32.2, B.R37.2, B.T11.D, B.T21.D, B.T31.D, B.U11.1, B.U21.1, B.U31.1
VCC1: I.J3.3, JP1.1, JP3.1, K.C1.1, K.C2.1, K.R1.1, K.R2.1, K.U1.VCC
VCC2: I.J1.3, JP5.1, JP6.1, K.C3.1, K.C4.1, K.R6.1, K.R7.1, K.U2.VCC
VCC3: D.C1.2, D.C7.2, D.J3.3, D.L1.2, D.R4.1, D.T2.G, D.U2.BP, D.U3.5
VMOT: D.C2.2, D.D2.K, D.F1.1, D.F2.1, D.R7.1, D.T1.S
VUSB3: D.C4.2, D.D2.A, D.J3.1, D.R6.2, D.R8.2, D.T1.G, U$3.A4B9, U$3.B4A9, U$4.4

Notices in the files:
parts and their libraries:
SparkFun-Connectors: Licensing: Creative Commons ShareAlike 4.0 International - https://creativecommons.org/licenses/by-sa/4.0
